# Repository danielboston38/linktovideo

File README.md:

# Link to Video

A replacement for the RF modulator in the original Nintendo Entertainment System (NES-001). Drops into the stock RF module slot inside the shell and provides composite video and USB-C power in place of a part that fails by design.

> [!CAUTION]
> **Safety advisory for boards built before 2026-09-08.**
> On every board fabricated so far, the USB-C VBUS input goes to F1 through 9.06 mm of
> 0.2 mm-wide trace. This trace becomes damaged at a current well below the guaranteed
> trip current of F1. If a fault occurs downstream, **F1 cannot protect the input
> trace on the board**.
> The defect has no effect on normal operation (48 °C, 17 mV drop). It is a
> fault-tolerance defect, not a wear-out defect. A board that works now will continue to work.
> Commit [`247334c`](../../commit/247334c) corrects the layout. The rework of an affected
> board takes approximately 15 minutes.
>
> **→ Read the full advisory: [docs/SAFETY-ADVISORY-2026-09-vbus-trace-ampacity.md](docs/SAFETY-ADVISORY-2026-09-vbus-trace-ampacity.md)**

> [!WARNING]
> **Safety advisory for boards built before C5 was added (2026-11-22).**
> If you plug a cable that is already live into the board, for example from a USB-A charger with an A-to-C cable,
> the voltage at U1's input can ring to about 9.5 V. The absolute maximum of U1 is 7 V.
> A USB-C charger or power bank with a C-to-C cable is safe, because it turns on 5 V only after it detects the board.
> The fix is a 100 µF electrolytic, C5, on U1's input. You can add it to an existing board in about 10 minutes.
>
> **→ Read the full advisory: [docs/SAFETY-ADVISORY-2026-11-hotplug-overshoot.md](docs/SAFETY-ADVISORY-2026-11-hotplug-overshoot.md)**

> **Renamed.** The first revision of this project had the name **Kirby's New Dream**.
> From v2, the name is **Link to Video**. Items with the old name are the same project:
> the v1 board silkscreen, the 2026-07-16 PCBWay fab package, and older commits.
> The GitHub repository also has the new name. The old `kirbysnewdream` URL still
> redirects to it.

## Why this board exists

The NES-001's RF modulator already carries composite video, so this isn't about
adding an output the console lacks. It's about replacing a part that reliably
destroys itself.

Nintendo packed the modulator's regulator and RF stages into a sealed can with no
ventilation. It cooks its own electrolytics, they leak, and the electrolyte eats
the traces underneath. Across three NES-001 units on the author's bench, **all
three** had modulator failures from exactly this — including a Mitsumi unit that
looked pristine externally and had every capacitor leaking inside.

So the modulator is a consumable on a forty-year-old console, and the usual
options are to recap a corroded board or to fit an aftermarket board. This is the
second option, with the power input modernised to USB-C while the slot is open.

## Disclosure

This project's schematic design, debugging, and documentation were developed with the assistance of AI (Claude, by Anthropic). All hardware was hand-assembled, tested, and validated by the author. Use, review, and verify independently before building.

## Status

🟡 First prototype assembled and power-tested successfully (5V confirmed clean on rail, no protection trips). Video output path **does not work on v1 hardware** — traced to a schematic defect in which Q1's emitter node was shorted to the +5V rail (see Known Issues). Fixed in source; v1 boards need a rework.

<!-- Swap the line above for something like this once video's confirmed:
🟢 Fully validated — power and composite video both confirmed working on hardware.
-->

## Features

- USB-C power input (power only, no data lines)
- Composite video output
- Active overcurrent protection: TPS2553 eFuse with a ~1.18 A resistor-programmed limit, soft-start and thermal shutdown, and a polyfuse as backup
- Fits inside the original NES shell at the stock RF module location
- Bring-up test points for video, ground, +5 V and audio, labeled on the silkscreen
- Header that feeds an external 8-pin mini-DIN RGB connector (NESRGB)
- All resistor and capacitor values printed on the silkscreen. On the v1 board, four identical axial footprints with no labels held four different values. This caused three wrong-resistor build errors.
- 2-layer PCB, designed in KiCad

## Power path

```
USB-C  ──  F1 polyfuse  ──  U1 TPS2553 eFuse  ──  +5V rail  ──  J4.3 → NES
  VBUS      2.0A hold        ~1.18A limit          C1 100µF
            3.8A trip        soft-start            D1 TVS
            (backup)         thermal shutdown
```

F1 alone trips at 3.8 A. The console draws approximately 0.5–0.7 A, so F1 alone
does not protect it. U1 gives the real protection. F1 is a backup if the eFuse
fails as a short circuit.

R6 on U1's ILIM pin sets the current limit. The relationship is
**inverse**: a larger resistor gives a *lower* limit.

| R6 | Limit (typ) |
|---|---|
| 15 kΩ | 1700 mA |
| 20 kΩ | 1295 mA |
| **22 kΩ (fitted)** | **~1180 mA** |
| 49.9 kΩ | 520 mA |
| 210 kΩ | 130 mA |

Approximately, I_OS(A) ≈ 25.9 / R6(kΩ). This equation is valid in the range that
TI recommends, 15 kΩ–232 kΩ.

U1's EN (pin 3) is active-high. It connects to U1's own input, so the switch is
always on. FAULT (pin 4) is an open-drain output with no connection. A closed NES
shell has no indicator for FAULT to drive. If you want a fault indicator, FAULT can
sink 25 mA directly.

**Useful side effect: a reversed D1.** D1 is a unidirectional TVS. If you install
D1 backwards, it puts a forward-biased diode across the 5 V rail. Before the board
had U1, this error made almost a short circuit. The only protection was the
polyfuse, which needs seconds to react. Now the eFuse limits the current to
~1.18 A and then does a thermal shutdown, so the error limits itself and does
not destroy parts.

## Test points (v2)

The board has four through-hole test points (2.0 mm pad, 1.0 mm drill) for bring-up.
Each test point accepts a 0.64 mm square header pin. You can solder pins into them
and attach scope grabbers.

The silkscreen shows only the signal name: `VIDEO`, `GND`, `+5V`, `AUDIO`, so
you can read the board without this table. The reference designator is on F.Fab,
for the fab drawings.

The first pass of v2 had this backwards. The signal names were on F.Fab, which does
not go onto the physical board. As a result, the silkscreen showed only `TP1`–`TP4`.

| TP  | Net          | Location (mm) | Notes |
|-----|--------------|---------------|-------|
| TP1 | `/VIDEO_OUT` | 62.0, 60.0    | Jack-side video: after C2 and the 75 Ω series resistor R5. This is the signal that the TV gets. A high-impedance probe reads approximately double the terminated amplitude. |
| TP2 | `GND`        | 58.5, 60.0    | Connects directly to the B.Cu ground pour. |
| TP3 | `/5V`        | 52.0, 43.1    | On the protected 5 V trunk, downstream of F1 and the TPS2553. |
| TP4 | `/AUDIO_OUT` | 65.9, 28.35   | Audio pass-through between J4 pin 2 and J2. |

The whole back layer is a ground pour, so TP2's position is for
convenience only. You can clip a ground lead to any B.Cu feature.

To probe the buffer and not its output, probe Q1's emitter leg directly.
`Net-(Q1-E)` has no test point.

## RGB output (v2)

This board can feed the RGB connector of the [NESRGB](https://etim.net.au/nesrgb/)
board. That connector uses the 8-pin mini-DIN standard of the Micomsoft XRGB-mini
Framemeister.

The connector is **not** on this board. The NESRGB kit supplies it as a panel-mount
jack. The jack attaches with epoxy in a 12 mm hole in the shell. This board only
feeds the jack. R/G/B go directly from the NESRGB to the connector. **J5** on this
board supplies the other three pins:

| J5 pin | Net          | mini-DIN pin | |
|--------|--------------|--------------|---|
| 1 | `/RGB_VIDEO` | 3 | Composite video / sync, 75 Ω terminated |
| 2 | `GND`        | 4 | |
| 3 | `/5V`        | 5 | Downstream of the TPS2553, so it is current-limited |

Mini-DIN pins 1 and 2 have no connection. Pins 6, 7 and 8 are Blue, Green and Red
from the NESRGB. The standard does not carry audio. Audio stays on the RCA jack.
Tim Worthington made this choice deliberately, because it keeps video noise out of
the audio.

**Why R7 exists.** The output of the video buffer (`/VIDEO_BUF`, Q1's emitter
through C2) now feeds two outputs. Each output needs its own 75 Ω source
termination: R5 for the RCA jack, R7 for the mini-DIN. One shared resistor puts two
75 Ω loads in parallel when both cables are connected, and cuts the amplitude by half.

**One output at a time.** Composite and RGB are alternatives. The design does not
target the use of both at the same time. The connected cable gets a correct 75 Ω
source. The unused branch is a stub with no load.

If both cables are connected at the same time, R7 still gives each output a
correctly terminated 75 Ω source. The amplitude does not decrease by half. In that
case, Q1's drive is the limit. For this reason, **R1 is 220 Ω from v2**, not
the original 330 Ω.

An ngspice simulation used 2 Vpp at the tap, with both outputs terminated. At
330 Ω, the follower clips the positive (white) peaks by 33 %. At 220 Ω, it clips
them by 11 %. With one output loaded (the supported mode), 220 Ω is clean and
symmetric (+0.439 / −0.447 V at the jack). These results come from simulation, not
from measurement on hardware. Two connected outputs are still not a supported mode.

## Hardware

- Designed in KiCad (schematic + PCB source included in this repo)
- Fabricated by PCBWay
- See [BOM.csv](./BOM.csv) for the full parts list

### Sponsored by PCBWay

The most recent fabrication run of this board — the 2026-08-26 package, ordered
**2026-08-27** — was
**sponsored by [PCBWay](https://www.pcbway.com/)**, who covered the manufacturing
of the boards this project is built and tested on. Thank you — having the fab
covered is what let this revision get made, populated and put on the bench rather
than staying a set of gerbers.

Those boards predate [`247334c`](../../commit/247334c), so like every board
fabricated so far they carry the `/raw_5v` trace-ampacity defect described in the
caution at the top of this file — see
[the safety advisory](docs/SAFETY-ADVISORY-2026-09-vbus-trace-ampacity.md).

PCBWay have been good to work with on the practical side too: the 2-layer,
1.6 mm FR4 board here is an unremarkable order for them, the gate-generated fab
package uploaded without any back-and-forth over the drill or layer files, and
they will run the four SMD lines (C3, R6, U1, USB-C1) as single-sided SMT while
leaving the through-hole parts to the bench — including sourcing the TPS2553
from LCSC, which DigiKey and Mouser have on a 112-day lead. See
[docs/pcbway-smd-assembly.md](./docs/pcbway-smd-assembly.md) for that workflow.

The project is also published on PCBWay's community site, with the same design
files and documentation as this repository:

**→ [Link to Video on PCBWay Community](https://www.pcbway.com/project/shareproject/Link_to_video_7f1f9279.html)**

The sponsorship covered fabrication only, and carries no editorial influence over
this documentation. The design remains [CERN-OHL-S v2](./LICENSE.txt) and
OSHWA-certified, free for anyone to study, modify, build and have made wherever
they like. The PCBWay-hosted copy is published under GPL v3 because their form
does not offer CERN-OHL-S — see [License](#license).

## Build Notes / Known Issues (v1)

- **Q1 emitter node shorted to +5 V (breaks video).** The rail clamps Q1's emitter,
  so C2 couples +5 V, not video, into R5/J3.

  The wiring is different in each revision. In the pre-v1.1 source in this
  repository, R1 had *both* ends on `/5V`. On the boards fabricated from the
  2026-07-16 gerbers, R1 pad 1 is on `/5V`. R1 pad 2 is on a separate net with only C1.

  Root cause: an edit on 2026-07-04 deleted an R2 (110 Ω) from the schematic. KiCad
  then merged the two remaining collinear wire stubs into one wire. That wire
  connected the emitter node to `/5V`. The source has the fix from v1.1. For the
  rework of an existing board, see
  [Q1 emitter rework (v1 boards)](#q1-emitter-rework-v1-boards).
- The mounting holes of the video/audio RCA jack are slightly asymmetric. This problem
  is cosmetic only. It has no effect on the fit in the NES shell.
- The v1 silkscreen has no component value labels and no pin markers (E/C/B) for Q1.
  **Values are on the silkscreen from v2.** R1/R3/R4/R5/R7 use one footprint with four
  values. On v1, this caused three wrong-resistor errors in R1: a 5.1 kΩ and an 820 Ω
  were both installed before the correct value. The silkscreen does not have Q1 pin
  markers yet.
- **VBUS input trace is undersized for its own fuse (all fabbed boards).** `/raw_5v`
  goes to F1 through 9.06 mm of 0.2 mm trace. At 2.22 A, the trace exceeds the glass
  transition of FR4. At 2.83 A, the trace chars. F1 (RHEF200) is guaranteed not to
  trip below 2.0 A. It is guaranteed to trip only above 3.8 A. In the 2.2–3.8 A
  window, the trace is destroyed and the fuse possibly never operates.

  Root cause: a gap in the netclass patterns. The patterns `/5V*`, `GND*` and `VBUS`
  assigned the `Power` class (0.8 mm). None of these patterns matched the actual net
  name `/raw_5v`, so the net got the `Default` class (0.2 mm). DRC cannot find this
  defect, because DRC enforces the board `min_track_width` (0.2 mm), not the netclass
  width. Commit `247334c` corrects the pattern and changes the route to 0.8 mm.
  **Existing boards need a rework.** See
  [the safety advisory](docs/SAFETY-ADVISORY-2026-09-vbus-trace-ampacity.md).

- **D1 does not protect U1.** The installed TVS is a Littelfuse 1.5KE6.8A: stand-off
  5.80 V, breakdown 6.45–7.14 V at 10 mA, clamping 10.5 V at 144.8 A. The absolute
  maximum of the TPS2553 on IN and OUT is 7 V. At the voltage where the eFuse goes out
  of specification, the TVS barely conducts. In a real surge, the TVS lets the rail
  reach 10.5 V. D1 protects the console downstream, but it does not protect U1.

  A different position for D1 does not help, because both U1 pins have the same 7 V
  rating. Also, no avalanche TVS clamps below 7 V and also stands off the 5.5 V worst
  case of USB-C. Correct protection needs a switch with an integrated overvoltage
  cutoff. That fix is for v3. v2 ships with this gap.
- D1's symbol (`Diode:1.5KExxA`) names the two pins A1/A2 and shows no cathode.
  KiCad uses the same pin names for the unidirectional and bidirectional variants of
  this part. Only the silkscreen band of the footprint shows the polarity. The band is
  at the pad-1 (+5 V) end, which is correct. Look at this band when you assemble by hand.

### Q1 emitter rework (v1 boards)

This procedure applies to the boards fabricated from the 2026-07-16 gerbers. The IPC
netlist of these boards reads:

- `/5V = J4.3, F1.1, R1.1, Q1.1, C2.1, D1.1`
- `Net-(C1-Pad1) = R1.2, C1.1`

That revision has two defects:

- The rail clamps Q1's emitter.
- C1 connects to the rail only through R1, so the bulk capacitor does not decouple
  the rail.

This procedure corrects the two defects together.

> [!CAUTION]
> **Do not apply power with Q1 installed before you complete the cut.** The short destroys transistors.
> The rail clamps the emitter at +5 V, and the base is at the video level of the NES.
> The B-E junction has a forward bias of 3–4 V. Q1 saturates, with its collector
> connected directly to ground. Nothing limits the current. Q1 is a 150 mA part, and F1
> does not trip until the current reaches 3.8 A. Each power-up in that condition can
> destroy another transistor. The first transistor probably failed this way.

**Confirm the diagnosis before you cut.**

1. Disconnect the power.
2. Make sure that the capacitors are discharged.
3. Put one meter lead on +5 V, at J4 pin 3 or at D1's K-marked lead.
4. Do the two measurements in the table. The results on a defective board and on a
   correct board are opposites:

| Measurement | Defective board | Correctly wired |
|---|---|---|
| Q1 emitter → +5 V | **~0 Ω** | ~330 Ω (R1) |
| C1 **+** terminal → +5 V | **~330 Ω** (stranded behind R1) | ~0 Ω |

After the rework, the two results change places.

To identify Q1's legs without the TO-92 orientation, measure each leg:

- 0 Ω to GND: collector
- Continuity to J4 pin 1: base
- The remaining leg: emitter

These two tests look useful, but they are not:

- **Emitter → J3 tip.** C2 blocks DC, so this test reads open on every board.
- **C1 + → Q1 emitter.** This test reads ~330 Ω on a good board *and* on a bad board.
  R1 is between these two points in both wirings, so the test cannot identify the
  defect.

With power on, the fastest check is the DC voltage at Q1's emitter. A correct
board shows approximately 1.5–3 V. A shorted board shows exactly the rail voltage.

**R1's left pad is a star point.** Three connections meet there:

- F1 (the source)
- The D1 + J4.3 branch (the load)
- Q1's emitter

The two rail traces that come in are *collinear*, so one cut severs both.
For this reason, the rework needs **two** jumpers, not one.

1. **Cut** the 0.8 mm trace that goes from R1's left pad toward the **upper
   left**. Make the cut approximately 5–8 mm from the pad.

   Do not cut the trace that comes in from the upper right. That trace is Q1's emitter
   and must stay.

   Make the cut below the level of the D1 cathode. Above that point, only one of the
   two overlapping traces is present. You must cut both traces.

2. **Install two jumpers.** Remove R1 before you install the jumpers. The right pad of
   R1 is much easier to solder when it is empty.

   After the cut, there are three islands. Connect all three islands into one rail:

   | Island | Pads |
   |---|---|
   | A | C1's **+** pad, R1's **right** pad |
   | B | F1 pad 1 (left pad, trace toward D1 — not the USB-C side) |
   | C | D1's cathode (K), J4 pin 3 |

   Any two wires that connect all three islands are correct. This example puts one
   wire on each pad:
   - **C1+ → F1 pad 1** (~14 mm)
   - **R1's right pad → D1 cathode** (~25 mm)

3. **Install R1 = 300–330 Ω.** Before you install the part, make sure that it is
   correct. R1, R3, R4, R5 (and R7 on v2) use the same `R_Axial_DIN0207` footprint
   with four different values. The v1 silkscreen shows no values.

   At least one board got a 5.1 kΩ resistor from the R3/R4 pile in the R1 position.
   With that resistor, the standing current is ~0.6 mA, not ~9 mA. The board looks
   plausible but gives no usable video.

4. **Make sure that R5 (75 Ω) is installed.** Measure across R5's pads. The
   result must be ~75 Ω. R5 has no parallel path in the circuit: C2 blocks DC on one
   side, and the jack is open on the other side, so this measurement is also a
   check of the meter.

5. **Install the transistor last.** If you apply power before you complete the cut,
   Q1 saturates. Current flows from the rail directly to ground with no limit. See the
   caution above.

Before you apply power, do these checks with a meter:

- R1 left pad to D1 cathode: **open**
- R1 left pad to F1 pad 1: **~330 Ω**, through R1
- R1 left pad to Q1's emitter and to C2 pin 1: continuity
- D1 cathode to J4 pin 3 *and* to F1 pad 1: **~0 Ω**

With power on, the correct voltage at Q1's emitter is approximately 1.5–3 V. If
the emitter reads 5 V, the cut did not separate the traces.

## Video input biasing

Q1's base is DC-coupled directly to the NES video line. This board has no bias
network. That design is deliberate. A long bench session was necessary to find out
why it works.

**The NES mainboard supplies a 1 kΩ pulldown on its video output pin.** The
in-circuit measurement is 0.999 kΩ, and it is the same with the meter leads in both
directions, so the pulldown is a real resistor, not a semiconductor junction. Q1's
base sources approximately 46 µA. That 1 kΩ resistor absorbs this current with
approximately 46 mV. The base cannot float up, and Q1 cannot cut off.

For the same reason, the original Nintendo modulator also has no base pulldown. It
also matches the load Nintendo presented on that pin: a 330 Ω series resistor into a
5.6 kΩ / 330 Ω divider, approximately 500 Ω in total. The NES is designed to drive a
few hundred ohms.

**So this board has no base pulldown and no input coupling capacitor.** If you
adapt this design for a device other than an NES-001, measure that pin to ground
first. If the pin reads open, add a pulldown (~47 kΩ). This board does not have one.

**R2 (330 Ω) is not a bias resistor.** R2 is in series between J4 pin 1 and Q1's base.
Nintendo puts a 330 Ω resistor in the same position. Q1's base input impedance
is ~21 kΩ, so R2 has almost no effect on the signal. R2 limits the fault
current into the base-emitter junction. The reverse rating of that junction is only
5 V.

## Design checks

This project uses three more checks in addition to ERC and DRC. The first two checks
find faults that this board actually shipped with. The third check covers the gap
between the check of a board and its fabrication.

### `tools/check_nets.py`

```
python3 tools/check_nets.py
```

This script does these steps:

1. It exports the schematic netlist.
2. It reads the pad nets from the PCB.
3. It makes sure that the two agree.
4. It asserts a set of invariants.

The most important invariant is that **Q1's emitter is not on any power net**.
That was the v1 fault. The output of the emitter follower connected to +5 V, with
J4.3, D1.1 and F1.1, so Q1 saturated into a grounded collector, and nothing limited
the current. Each power-up destroyed a transistor.

**ERC and DRC both passed on that board with no errors.** Neither check can see that a
net is *wrong*. They can see only that a net is internally consistent. This script
exists for that reason.

Run this script before you generate a fab package. Gerbers contain no net
information. After you generate them, the mistake is invisible.

### `nes_power_video.kicad_dru`

Custom DRC rules for the geometric half of the problem:

- More clearance between the supply rails and the emitter and base nodes
- More clearance between the two USB-C configuration channels

These rules find the same mistakes when they occur as adjacent copper in the layout.
They cannot find an incorrect net assignment, because DRC has no information about
design intent. The script above does that check.

### `prefab-gate`

```
export KICAD_CLI=/Applications/KiCad/KiCad.app/Contents/MacOS/kicad-cli
prefab_gate package nes_power_video.kicad_pcb --out pcbway_production
```

**prefab-gate is now in its own repository:
[danielboston38/prefab-gate](https://github.com/danielboston38/prefab-gate).**
prefab-gate is a general-purpose KiCad tool. It has its own users and its own MIT
license, so it is no longer part of a hardware project.

To install prefab-gate, use one of these methods:

- Install it as a KiCad plugin through the Plugin and Content Manager.
- Install it as a Claude Code plugin: `/plugin marketplace add danielboston38/prefab-gate`
- Clone the repository and run `scripts/prefab_gate.py` directly.

The gate refuses to write a fab package for a board that did not pass DRC with zone
refill *and* schematic parity. After the refill, the gate calculates a hash of the
board and the schematic. Before it publishes the package, it checks them again,
so the package always describes the board that the gate actually verified.
`manifest.json` records this result with every finding, including the cosmetic
findings that the gate waived.

To get the verdict without writing files, run `check` instead of `package`.

Git does not track `pcbway_production/`, because you can make the packages again from
the board. The first two fab packages are still in the git history, at the 2026-07-07
and 2026-07-16 commits. The 2026-08-26 package for the sponsored run is not in a
commit. But a check found that its copper and outline gerbers are byte-identical to
the board at [`f672f8d`](../../commit/f672f8d), and all 49 drill hits match.

When you order, generate a new fab package. Do not use an old directory. The gate then
verifies again the board that you will pay for.

## Assembly

<!-- Add step-by-step or reference photos here once you've got a documented build process -->

See BOM.csv for the exact part values and footprints. Each component has its sourcing
data in two places, and the two places agree:

- The `Manufacturer`, `MPN`, `LCSC`, `Supplier Link` and `Datasheet` fields on the
  schematic symbol
- The matching columns in `BOM.csv`

Generic passives have no manufacturer part number, by design. They have a `Spec` field
instead (tolerance, rating, package). Any part that meets that specification is
correct. To get the fields directly from the schematic, run this command:

```
kicad-cli sch export bom --group-by '' \
    --fields 'Reference,Value,Manufacturer,MPN,LCSC,Datasheet,Supplier Link,Spec' \
    -o bom.csv nes_power_video.kicad_sch
```

The `Mount` column in `BOM.csv` marks each line `SMD` or `THT`. The value comes from
the attributes of the footprint on the board.

### Having PCBWay fit the SMD parts

Only four parts need reflow: C3, R6, U1 and USB-C1. All four are on the top side,
so PCBWay can do single-sided SMT, and you solder the 15 through-hole parts. Then
you do not solder the two most difficult joints on the board (the SOT-23-6 and the
Type-C receptacle). You also do not pay for full assembly.

`tools/pcbway_assembly.py` makes the SMD-only upload pair from a fab package that the
gate generated. The script gets the SMD/THT split from the board, not from a manual
list:

```
python3 tools/pcbway_assembly.py nes_power_video.kicad_pcb pcbway_production/<timestamp>
```

Before you order, read these two items:

- **U1 is out of stock at both DigiKey and Mouser** (112-day factory lead). LCSC has
  44,000. Tell PCBWay to get U1 from LCSC.
- **USB-C1 is Hybrid, not SMD.** Its four shell stakes are through-hole pads on the
  paste layer. They must reflow pin-in-paste with the other parts. Do not leave them dry.

From v2, all four SMD lines (C3, R6, U1, USB-C1) are LCSC parts, so PCBWay can get
the full assembly BOM from LCSC. For full details, including what to upload and what
not to upload, see **[docs/pcbway-smd-assembly.md](./docs/pcbway-smd-assembly.md)**.

Key notes:
- D1 (zener/TVS): put the cathode (banded end) toward the VBUS/+5V side. From v2, the
  silkscreen shows the installed value, `1.5KE6.8A`. Before v2, the silkscreen showed
  the generic KiCad symbol name `1.5KExxA`. You cannot order a part with that name.
- Q1 (**2SA733**, PNP): hold the part with the flat side toward you and the leads down.
  The pins are then Emitter-Collector-Base, from left to right.
  This replaces the 2SA1015/KSA1015, **both of which are end of life** (checked 2026-08-29): MCC's
  `2SA1015-GR-AP` is stocked at Mouser but flagged End of Life, and every onsemi `KSA1015` reads
  Obsolete on DigiKey, available only through Rochester Electronics' last-time-buy channel. The
  2SA733 is in current production, shares the E-C-B pin order exactly so it drops straight in, and is
  a better part for a video buffer: f_T 190 MHz typ against the 2SA1015's 80 MHz, C_ob 2–3 pF, P_C
  750 mW, with the same V_CEO −50 V / I_C −150 mA / V_EBO −5 V — so R2 still guards the base-emitter
  junction exactly as before. Buy the UTC `2SA733L-P-T92-B` from LCSC (**C5310429**, ~$0.035).
  Rank P is hFE 200–400, which matches the ~46 µA base current measured on the bench, so the bias
  point does not move. DigiKey's Renesas 2SA733 is Rochester stock at $1.90 — same trap, different part.
- **Why not a 2N3906 or BC557?** Not for the reason you might assume. Electrically the 2N3906 is
  perfectly happy here — V_CEO −40 V, I_C −200 mA, f_T 250 MHz, V_EBO −5 V, hFE 100–300 at 10 mA,
  every figure with huge margin against a 5 V rail at ~9.3 mA. The problem is the middle pin. Per
  UTC's ordering tables, the 2N3906 is **E-B-C** and the 2SA733 is **E-C-B**: the 3906 puts *base* in
  the centre where this board wants *collector*. Turning the part around gives C-B-E — base is still
  in the middle, so no orientation fixes it and you would have to cross two leads. On a v3 layout the
  pin order is free and the 2N3906 becomes a fine choice; on this board it is not. Pin order is a
  manufacturer's choice rather than a standard, so check the datasheet of the exact brand you buy.
- R1 (220 Ω): the emitter load for Q1. One end connects to +5 V, and the other end
  connects to the Q1 emitter / C2 node. Both ends on +5 V is incorrect. v2 changed R1
  from 300 Ω to 220 Ω to increase the drive current. With the assumed base voltage of
  ~1.3 V, 300–330 Ω gives only ~6.2 mA at peak white. The 150 Ω load needs ~6.7 mA. If
  the measured DC at J4 pin 1 is not ~1.3 V, calculate R1 again.
- R2 (330 Ω): series resistor in the video input line, between J4 pin 1 and Q1's base. See [Video input biasing](#video-input-biasing).
- **Trim all through-hole leads flush.** The board is in the RF module slot, with
  shielding immediately below it. Long leads on the bottom side will touch the can and
  cause a short circuit. On the prototype, this short caused an intermittent supply
  trip. The trip occurred only when the board moved.
- C2 (470 µF): do not use 100 µF. Into the 150 Ω load, 100 µF gives τ=15 ms, but the
  field period is 16.7 ms. As a result, the picture tilts from top to bottom. 470 µF
  gives τ=70 ms.
- F1 (polyfuse): a small standoff above the PCB is correct. This standoff is normal for
  radial-lead parts and is not a defect.

  **KiCad has no footprint for the Littelfuse RHEF series.** F1 borrows
  `Fuse:Fuse_Bourns_MF-RG300`: pads 5.24 mm center-to-center, with 1.01 mm drills. The
  RHEF200 has 0.51 mm leads at 5.05 ±0.75 mm spacing, and these leads fit easily. But
  the Bourns device has a rating of 3.0 A/5.1 A, and the silkscreen outline shows *its*
  body. Use the outline only as an approximate guide, not as a clearance boundary. A
  correct RHEF200 footprint moves pad 2 by ~1.2 mm and makes a new route necessary,
  so that change is for v3, not a patch.

  **F1 stays a Littelfuse RHEF200 and is deliberately not an LCSC part.** F1 is
  through-hole, so it is not on the SMD assembly BOM that PCBWay sources. Also, the
  LCSC alternatives are worse in the important specifications:
  - Jinrui JK30-200 (C369104): I_max decreases to 40 A, and the part is 15.2 mm tall.
  - JKSEMI JK16-200T (C5183874): LCSC lists it as through-hole. But its datasheet has
    the title *"JK16 Series Surface Mount PTC Devices"* and shows no land pattern.
    Its package is unconfirmed.

  If you must order F1 again, buy it from DigiKey or Mouser with the Switchcraft RCA
  jacks. LCSC cannot supply those jacks either.
- USB-C1: GCT USB4125-GF-A-0190, SMD receptacle. Power-only, 6P, no data lines,
  48 V / 3 A, 20,000 mating cycles.

  **From v2, this part replaces the GCT USB4970-00-A.** LCSC does not stock the
  USB4970-00-A. A search for that MPN on LCSC always gives no results. The USB4125 is a
  different GCT line number, and LCSC *does* stock it (C5246813). The board layout
  already used its land pattern, so this change affects sourcing only, not the layout.

  The footprint is `Connector_USB:USB_C_Receptacle_GCT_USB4125-xx-x-0190`. Its copper,
  silk, fab, courtyard and drills are byte-identical to the plain `USB4125-xx-x`
  variant that the board used before. Only the name, the descr field and the 3D model
  are different.

  Use the **-0190** variant. It has the 1.90 mm shell stake, which extends 0.30 mm
  through this 1.6 mm board and gives a fillet on the bottom side. The 1.00 mm stake
  (plain `USB4125-GF-A`, C3151650) does not go through the board. LCSC has less stock
  of this part than of the generic Chinese 6P parts. Order spares.
- U1 (TPS2553, SOT-23-6): pin 1 is IN. The dot on the package marks pin 1. The pin order
  is IN, GND, EN down one side, and OUT, ILIM, FAULT up the other side. Order the plain
  TPS2553DBVR. The `-1` suffix is the latch-off variant. After each trip, that variant
  needs a power cycle. The plain part tries again automatically.
- C3 (100 nF, 0805): TI requires C3 as near to U1 pin 1 as the layout permits. C3 is
  immediately to the left of U1.
- R6 (22k, 0805): sets the current limit. Before you use a different value, see the
  table in Power path.

## Certification

This project is **OSHWA-certified open source hardware**, UID **[US002842](https://certification.oshwa.org/us002842.html)**.

The certification confirms two facts about the design files, schematics, PCB layout,
bill of materials and documentation in this repository:

- They are published under an OSI/FSF-approved open license.
- They are complete enough for another person to study, modify, manufacture and
  distribute the hardware.

See the [OSHWA certification directory entry](https://certification.oshwa.org/us002842.html)
for the registered details.

The certification mark above is
[`certification-mark-US002842-stacked.svg`](./certification-mark-US002842-stacked.svg).
OSHWA issued it for this UID. The mark applies only to this design. You cannot
transfer it to derivative designs. Each derivative needs its own certification.

## License

Licensed under [CERN-OHL-S v2](./LICENSE.txt) (strongly reciprocal open hardware license). See [LICENSE](./LICENSE.txt).

**The PCBWay community copy is GPL v3.** The project form on PCBWay does not offer
CERN-OHL-S, so the copy
[on their community site](https://www.pcbway.com/project/shareproject/Link_to_video_7f1f9279.html)
has a GPL v3 license. The design and the files are the same, with two license grants.
Use the grant under which you got the design. Both licenses are copyleft, and both are
on the approved list, so the certification holds with either license.

The practical difference is the physical board. CERN-OHL-S applies to the *making* of
hardware. If a person builds and sells a board, CERN-OHL-S requires the complete source
to go with that board. The copyleft of GPL v3 starts when a person distributes the
design files, so it does not apply to a board fabricated from those files. Both
licenses keep reciprocity for the design files. Only CERN-OHL-S gives reciprocity for
manufactured hardware.

## Photos

<!-- Add build photos here -->

## Acknowledgments

- **[PCBWay](https://www.pcbway.com/)** — for sponsoring the fabrication of the
  latest revision of this board, and for hosting the project on their community
  site: [Link to Video](https://www.pcbway.com/project/shareproject/Link_to_video_7f1f9279.html).
- **Tim Worthington** — for the [NESRGB](https://etim.net.au/nesrgb/), whose
  8-pin mini-DIN pinout J5 on this board feeds.
- **OSHWA** — for the open hardware certification programme
  ([US002842](https://certification.oshwa.org/us002842.html)).

<!-- Optional: credit anyone who helped with debugging, Discord community, etc. -->

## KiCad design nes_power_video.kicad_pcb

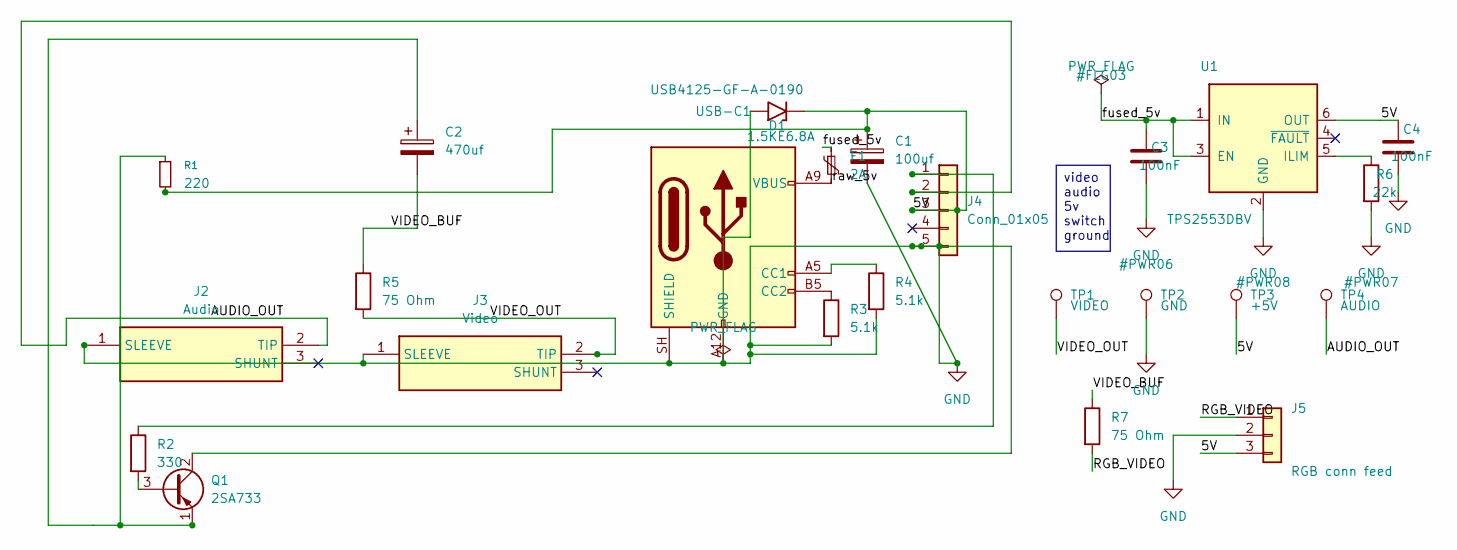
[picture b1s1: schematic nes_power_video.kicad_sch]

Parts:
C1: 100uf; CP_Radial_D10.0mm_P5.00mm
C2: 470uf; CP_Radial_D10.0mm_P5.00mm
C3, C4: 100nF; C_0805_2012Metric_Pad1.18x1.45mm_HandSolder; MPN CC0805KRX7R9BB104; LCSC C49678
D1: 1.5KE6.8A; D_DO-201AE_P15.24mm_Horizontal; MPN 1.5KE6.8A; LCSC C294199
F1: 2A; Fuse_Bourns_MF-RG300; MPN RHEF200
J2: Audio; PJRAN1X1U03X; Mouser Part Number 502-PJRAN1X1U03X
J3: Video; PJRAN1X1U03X; Mouser Part Number 502-PJRAN1X1U03X
J4: Conn_01x05; PinHeader_1x05_P2.54mm_Vertical
J5: RGB conn feed; PinHeader_1x03_P2.54mm_Vertical
Q1: 2SA733; TO-92_Inline; MPN 2SA733L-P-T92-B; LCSC C5310429
R1: 220; R_Axial_DIN0207_L6.3mm_D2.5mm_P7.62mm_Horizontal
R2: 330; R_Axial_DIN0207_L6.3mm_D2.5mm_P7.62mm_Horizontal
R3, R4: 5.1k; R_Axial_DIN0207_L6.3mm_D2.5mm_P7.62mm_Horizontal
R5, R7: 75 Ohm; R_Axial_DIN0207_L6.3mm_D2.5mm_P7.62mm_Horizontal
R6: 22k; R_0805_2012Metric_Pad1.20x1.40mm_HandSolder; MPN 0805W8F2202T5E; LCSC C17560
TP1: VIDEO; TestPoint_THTPad_D2.0mm_Drill1.0mm
TP2: GND; TestPoint_THTPad_D2.0mm_Drill1.0mm
TP3: +5V; TestPoint_THTPad_D2.0mm_Drill1.0mm
TP4: AUDIO; TestPoint_THTPad_D2.0mm_Drill1.0mm
U1: TPS2553DBV; SOT-23-6_Handsoldering; MPN TPS2553DBVR; LCSC C55266
USB-C1: USB4125-GF-A-0190; USB_C_Receptacle_GCT_USB4125-xx-x-0190_6P_TopMnt_Horizontal; MPN USB4125-GF-A-0190; LCSC C5246813

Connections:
/5V: C1.1, C4.1, D1.1 (A1), J4.3, J5.3, R1.2, TP3.1, U1.6 (OUT)
/AUDIO_OUT: J2.2 (TIP), J4.2, TP4.1
/RGB_VIDEO: J5.1, R7.2
/VIDEO_BUF: C2.2, R5.1, R7.1
/VIDEO_OUT: J3.2 (TIP), R5.2, TP1.1
/fused_5v: C3.1, F1.1, U1.1 (IN), U1.3 (EN); also elsewhere on the board
/raw_5v: F1.2, USB-C1.A9 (VBUS), USB-C1.B9 (VBUS)
GND: C1.2, C3.2, C4.2, D1.2 (A2), J2.1 (SLEEVE), J3.1 (SLEEVE), J4.5, J5.2, Q1.2 (C), R3.2, R4.2, R6.2, TP2.1, U1.2 (GND), USB-C1.A12 (GND), USB-C1.B12 (GND), USB-C1.SH (SHIELD); also elsewhere on the board
unnamed: J4.1, R2.1
unnamed: Q1.3 (B), R2.2
unnamed: C2.1, Q1.1 (E), R1.1
unnamed: R6.1, U1.5 (ILIM)
unnamed: R4.1, USB-C1.A5 (CC1)
unnamed: R3.1, USB-C1.B5 (CC2)

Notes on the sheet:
video audio 5v switch ground

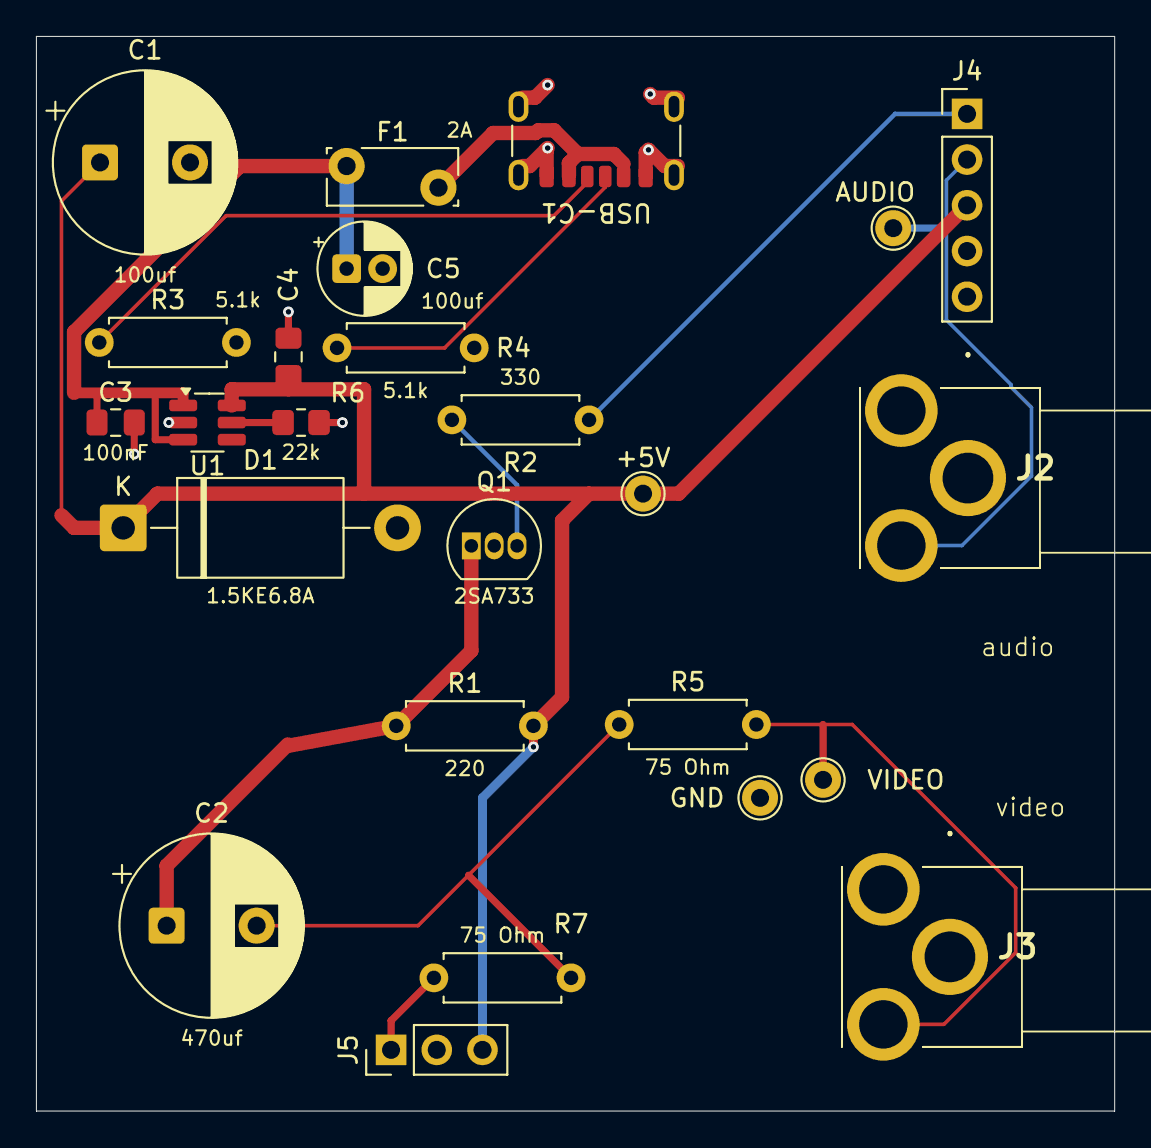
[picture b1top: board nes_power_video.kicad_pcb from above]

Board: 2 copper layers, 59.9 x 59.7 mm, 25 parts (0 on the bottom side), 14 nets.

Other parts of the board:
C5: 100uf; CP_Radial_D5.0mm_P2.00mm

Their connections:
/fused_5v: C5.1; also elsewhere on the board
GND: C5.2; also elsewhere on the board
